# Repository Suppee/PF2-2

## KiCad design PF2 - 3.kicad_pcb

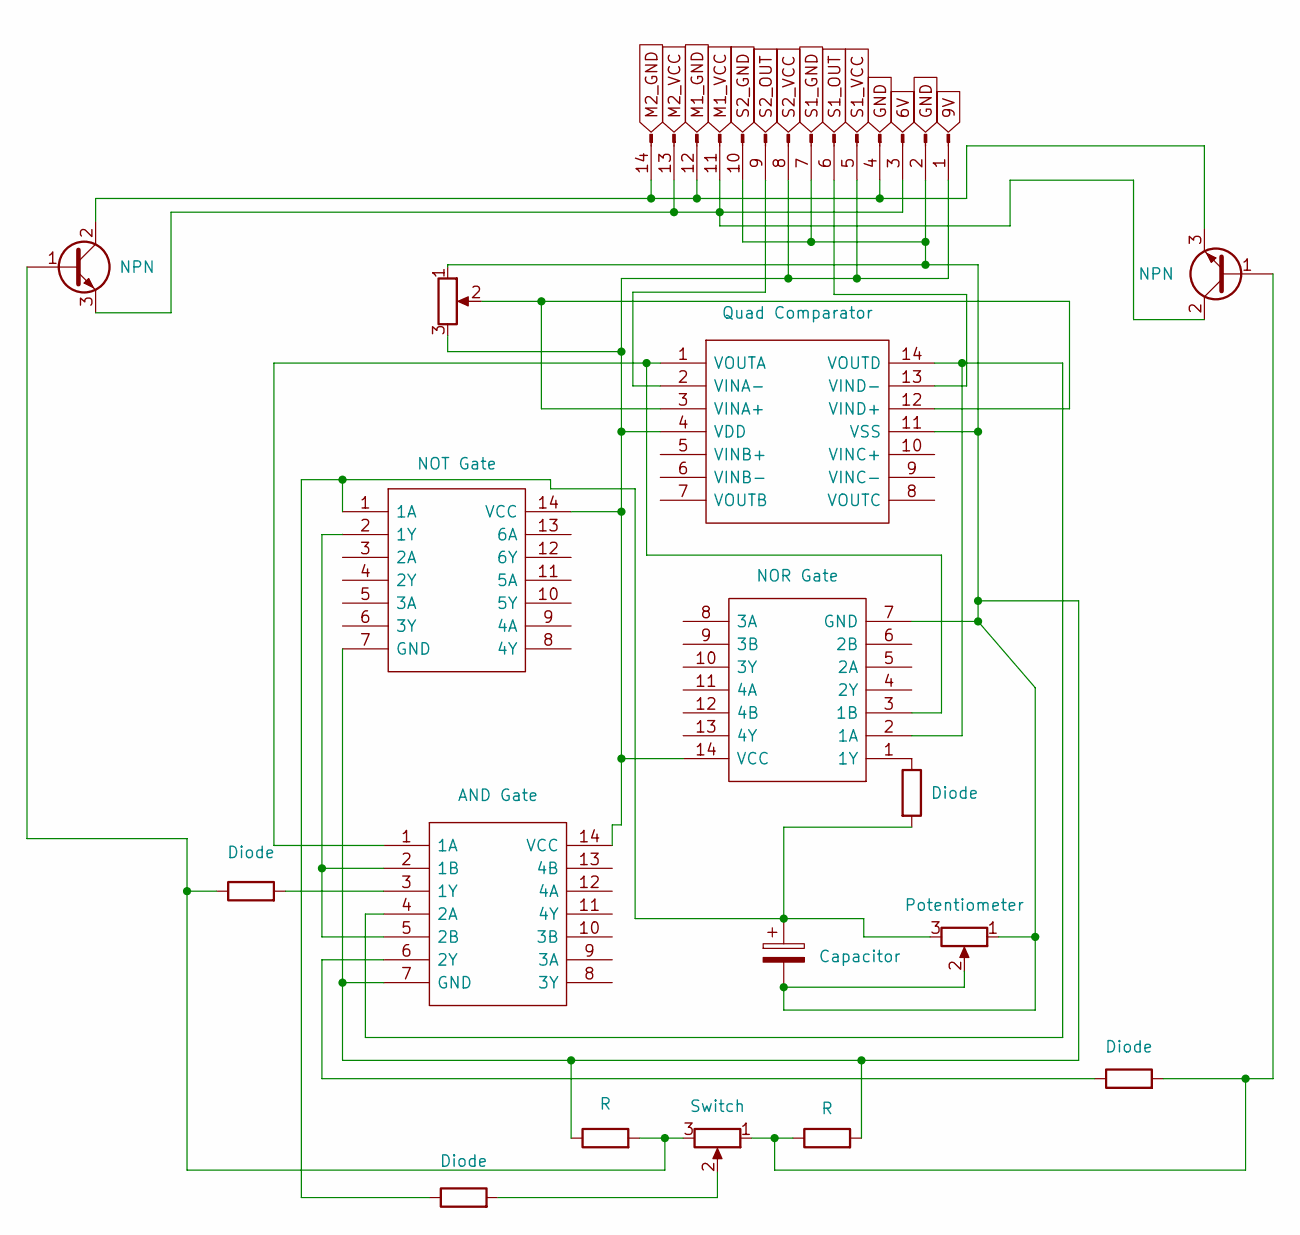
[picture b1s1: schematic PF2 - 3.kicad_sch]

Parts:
C1: Capacitor; R_Axial_DIN0207_L6.3mm_D2.5mm_P7.62mm_Horizontal
IC1: Quad Comparator; DIP762W53P254L1902H420Q14N; Manufacturer_Part_Number MCP6004T-E/SLVAO; Mouser Part Number 579-MCP6004T-E/SLVAO
IC2: NOT Gate; DIP762W53P254L1902H420Q14N; Manufacturer_Part_Number 74HC04N,652
IC3: AND Gate; DIP762W53P254L1902H420Q14N; Manufacturer_Part_Number 74HC08N
IC5: NOR Gate; DIP762W53P254L1902H420Q14N; Manufacturer_Part_Number 74HC02N,652; Mouser Part Number 771-74HC02N
J1: Conn_01x14_Male; Stocko_MKS_1664-6-0-1414_1x14_P2.50mm_Vertical
Q1, Q2: NPN; TO254P470X1028X1955-3P
R1, R2, R9, R10: Diode; R_Axial_DIN0207_L6.3mm_D2.5mm_P10.16mm_Horizontal
R7, R8: R; R_Axial_DIN0207_L6.3mm_D2.5mm_P10.16mm_Horizontal
RV1: (no value)
RV2: Switch; Potentiometer_Alps_RK163_Single_Horizontal
RV3: Potentiometer; Potentiometer_Alps_RK163_Single_Horizontal

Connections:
unnamed: C1.1, IC2.1 (1A), R2.2, R9.1, RV3.3
unnamed: C1.2, IC1.11 (VSS), IC2.7 (GND), IC3.7 (GND), IC5.7 (GND), J1.2, J1.7, J1.10, R7.2, R8.1, RV1.1, RV3.1, RV3.2
unnamed: IC1.1 (VOUTA), IC3.1 (1A), IC5.3 (1B)
unnamed: IC1.2 (VINA-), J1.9
unnamed: IC1.3 (VINA+), IC1.12 (VIND+), RV1.2
unnamed: IC1.4 (VDD), IC2.14 (VCC), IC3.14 (VCC), IC5.14 (VCC), J1.1, J1.5, J1.8, RV1.3
unnamed: IC1.13 (VIND-), J1.6
unnamed: IC1.14 (VOUTD), IC3.4 (2A), IC5.2 (1A)
unnamed: IC2.2 (1Y), IC3.2 (1B), IC3.5 (2B)
unnamed: IC3.3 (1Y), R1.2
unnamed: IC3.6 (2Y), R10.1
unnamed: IC5.1 (1Y), R2.1
unnamed: J1.3, J1.11, J1.13, Q1.3 (E), Q2.2 (C)
unnamed: J1.4, J1.12, J1.14, Q1.2 (C), Q2.3 (E)
unnamed: Q1.1 (B), R1.1, R8.2, RV2.3
unnamed: Q2.1 (B), R7.1, R10.2, RV2.1
unnamed: R9.2, RV2.2

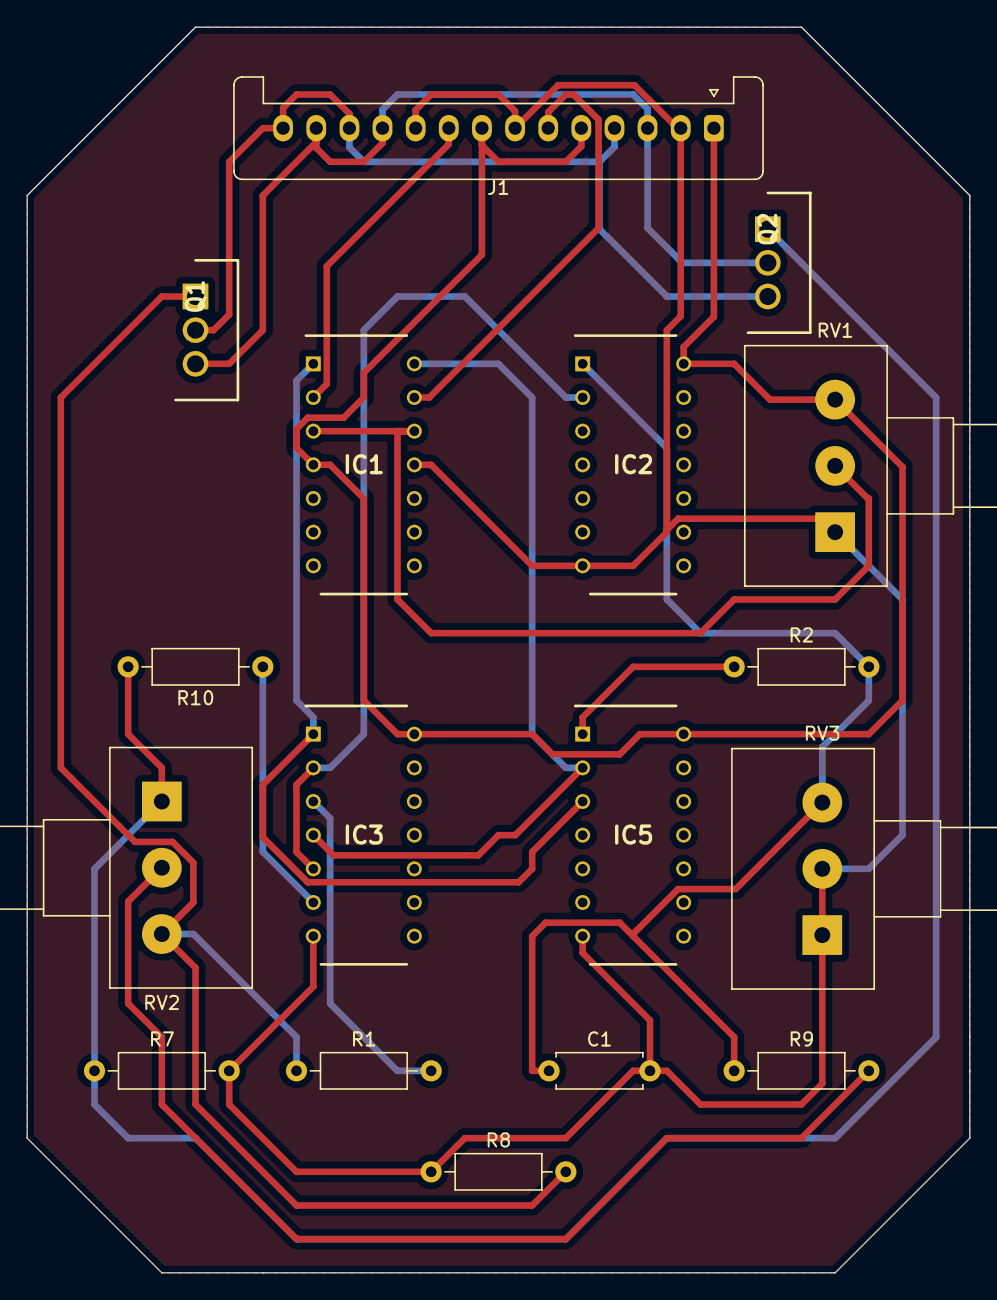
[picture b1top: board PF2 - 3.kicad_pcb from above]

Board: 2 copper layers, 71.1 x 94.0 mm, 17 parts (0 on the bottom side), 17 nets.

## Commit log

2022-11-17 KiCadFiles
